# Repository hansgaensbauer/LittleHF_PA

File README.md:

# Little HF MRF101AN PA

This is a HF power amplifier using the MRF101AN RF LDMOS transistor.

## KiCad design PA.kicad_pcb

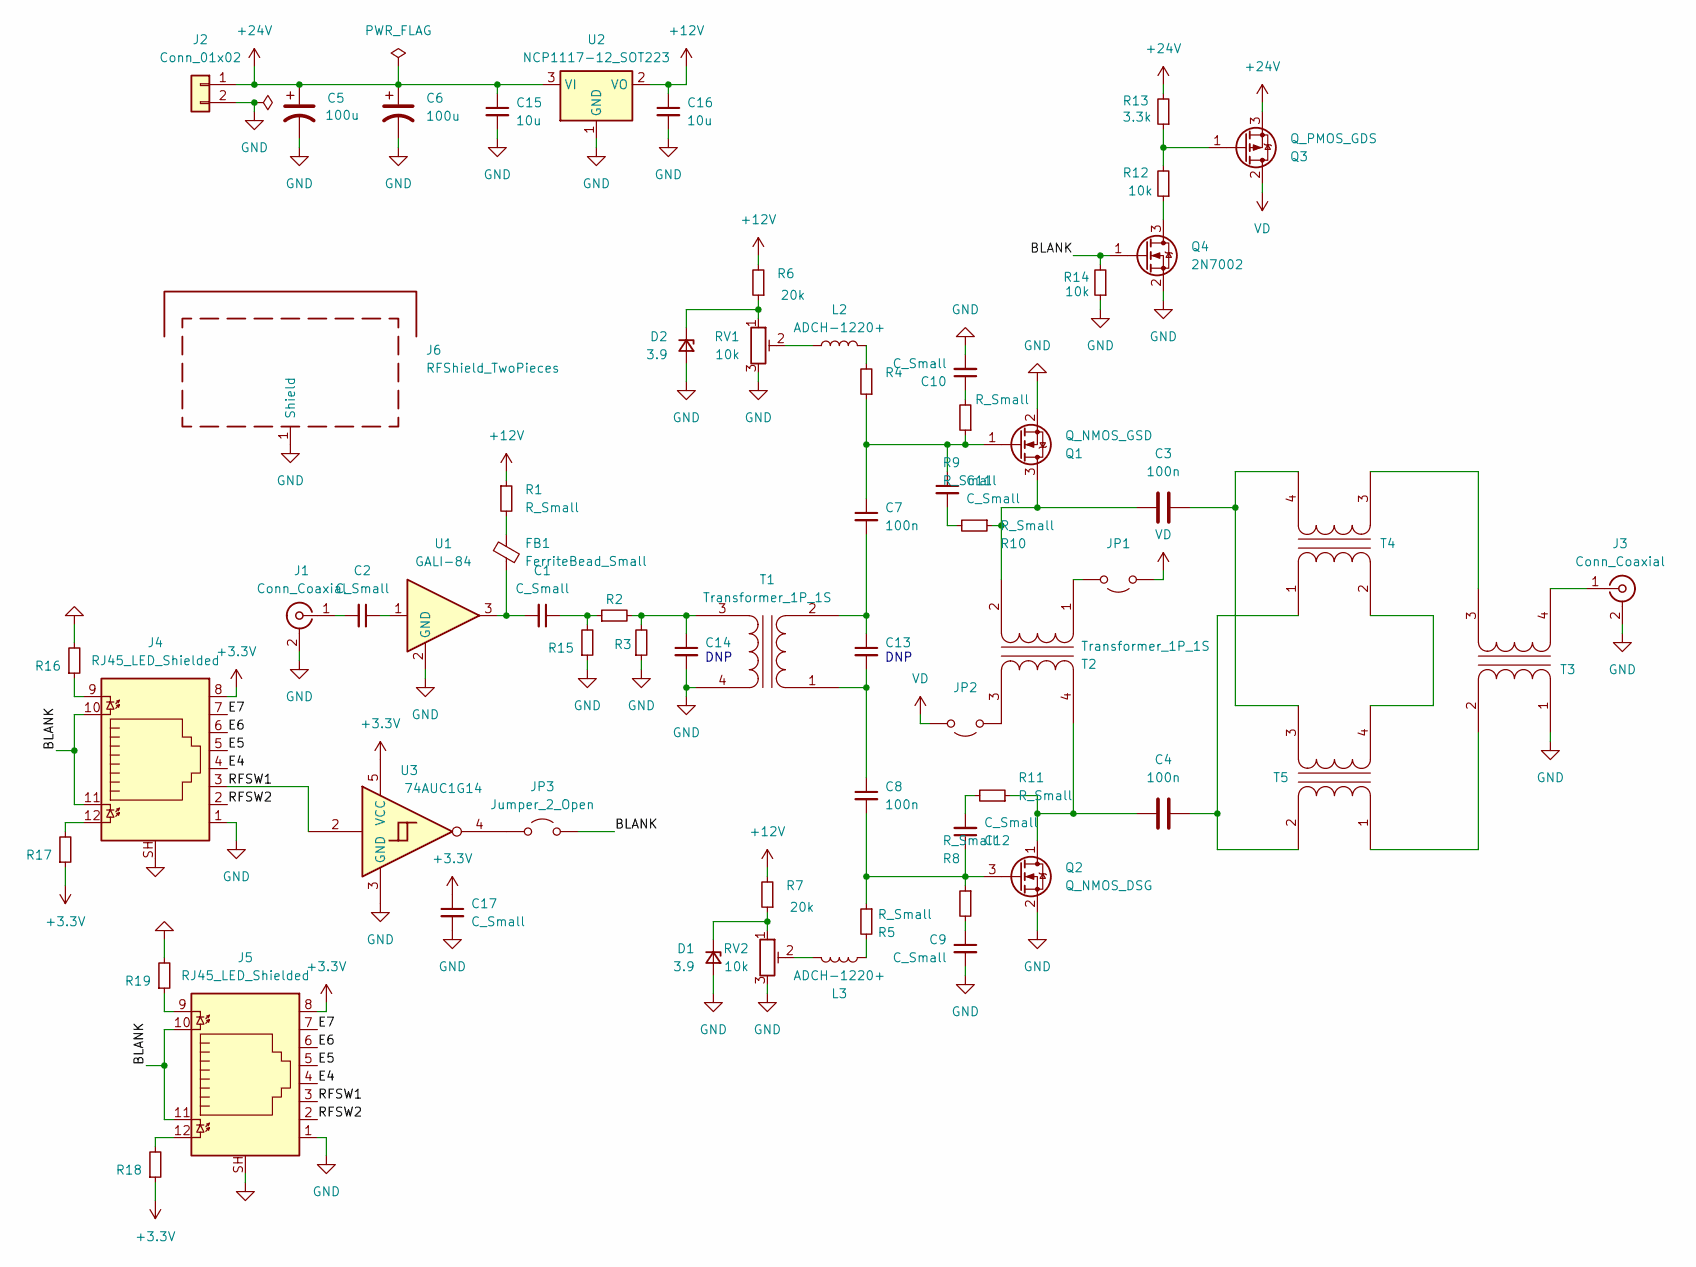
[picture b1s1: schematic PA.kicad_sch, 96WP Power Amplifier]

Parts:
C1, C2, C9, C10, C11, C12, C17: C_Small; C_0603_1608Metric
C3, C4: 100n; C_1812_4532Metric
C5, C6: 100u; CP_Elec_10x12.5
C7, C8, C13, C14: 100n; C_0603_1608Metric
C15, C16: 10u; C_1206_3216Metric
D1, D2: 3.9; D_SOD-123
FB1: FerriteBead_Small; L_1206_3216Metric
J1: Conn_Coaxial; SMA_Samtec_SMA-J-P-X-ST-EM1_EdgeMount
J2: Conn_01x02; Powerpole_1x2
J3: Conn_Coaxial; 538-73171-0780
J4, J5: RJ45_LED_Shielded; RJ45_Amphenol_RJHSE538X
J6: RFShield_TwoPieces; Wuerth_36103205_20x20mm
JP1, JP2: Jumper_2_Open; PinHeader_1x02_P2.54mm_Vertical_SMD_Pin1Left
JP3: Jumper_2_Open; R_0603_1608Metric
L2, L3: ADCH-1220+; Mini-Circuits_CD637_H5.23mm
Q1: Q_NMOS_GSD; TO-220-3_Horizontal_SMD
Q2: Q_NMOS_DSG; TO-220-3_Horizontal_SMD
Q3: Q_PMOS_GDS; TO-252-2
Q4: 2N7002; SOT-23
R1, R2, R3, R4, R5, R8, R9, R10, R11, R15, R16, R17, R18, R19: R_Small; R_0603_1608Metric
R6, R7: 20k; R_0603_1608Metric
R12, R14: 10k; R_0603_1608Metric
R13: 3.3k; R_0603_1608Metric
RV1, RV2: 10k; Potentiometer_Bourns_3269W_Vertical
T1: Transformer_1P_1S; Transformer_1P1S_13x13_Binocular
T2: Transformer_1P_1S; Transformer_Toroid_Horizontal_D18.0mm
T3, T4, T5: Transformer_1P_1S; Transformer_TLT_29x30
U1: GALI-84; SOT-89-3
U2: NCP1117-12_SOT223; SOT-223-3_TabPin2
U3: 74AUC1G14; SOT-23-5

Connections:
+3.3V: C17.1, J4.8, J5.8, R17.1, R18.1, U3.5 (VCC)
+12V: C16.1, R1.1, R6.2, R7.2, U2.2 (VO)
+24V: C5.1, C6.1, C15.1, J2.1, Q3.3 (S), R13.2, U2.3 (VI)
/BLANK: J4.10, J4.11, J5.10, J5.11, JP3.2 (B), Q4.1 (G), R14.2
/E4: J4.4, J5.4
/E5: J4.5, J5.5
/E6: J4.6, J5.6
/E7: J4.7, J5.7
/RFSW1: J4.3, J5.3, U3.2
/RFSW2: J4.2, J5.2
GND: C5.2, C6.2, C9.2, C10.2, C14.2, C15.2, C16.2, C17.2, D1.2 (A), D2.2 (A), J1.2 (Ext), J2.2, J3.2 (Ext), J4.1, J4.SH, J5.1, J5.SH, J6.1 (Shield), Q1.2 (S), Q2.2 (S), Q4.2 (S), R3.1, R14.1, R15.1, R16.2, R19.2, RV1.3, RV2.3, T1.4 (SB), T3.1 (AA), U1.2 (GND), U2.1 (GND), U3.3 (GND)
unnamed: C1.1, R2.1, R15.2
unnamed: C1.2, FB1.2, U1.3
unnamed: C2.1, U1.1
unnamed: C9.1, R8.2
unnamed: C10.1, R9.2
unnamed: C11.2, R10.2
unnamed: C12.2, R11.2
unnamed: D1.1 (K), R7.1, RV2.1
unnamed: D2.1 (K), R6.1, RV1.1
unnamed: FB1.1, R1.2
unnamed: C2.2, J1.1 (In)
unnamed: J3.1 (In), T3.4 (SB)
unnamed: J4.9, R16.1
unnamed: J4.12, R17.2
unnamed: J5.9, R19.1
unnamed: J5.12, R18.2
unnamed: JP1.2 (B), T2.1 (AA)
unnamed: JP2.2 (B), T2.3 (SA)
unnamed: JP3.1 (A), U3.4
unnamed: L2.4 (RFGND), RV1.2
unnamed: L2.1 (RFIN), R4.2
unnamed: L3.4 (RFGND), RV2.2
unnamed: L3.1 (RFIN), R5.2
unnamed: C3.1, Q1.3 (D), R10.1, T2.2 (AB)
unnamed: C7.1, C11.1, Q1.1 (G), R4.1, R9.1
unnamed: C4.1, Q2.1 (D), R11.1, T2.4 (SB)
unnamed: C8.2, C12.1, Q2.3 (G), R5.1, R8.1
unnamed: Q3.1 (G), R12.2, R13.1
unnamed: Q4.3 (D), R12.1
unnamed: C8.1, C13.2, T1.1 (AA)
unnamed: C7.2, C13.1, T1.2 (AB)
unnamed: C14.1, R2.2, R3.2, T1.3 (SA)
unnamed: T3.2 (AB), T5.1 (AA)
unnamed: T3.3 (SA), T4.3 (SA)
unnamed: C4.2, T4.1 (AA), T5.2 (AB)
unnamed: T4.2 (AB), T5.4 (SB)
unnamed: C3.2, T4.4 (SB), T5.3 (SA)
VD: JP1.1 (A), JP2.1 (A), Q3.2 (D)

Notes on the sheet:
DNP

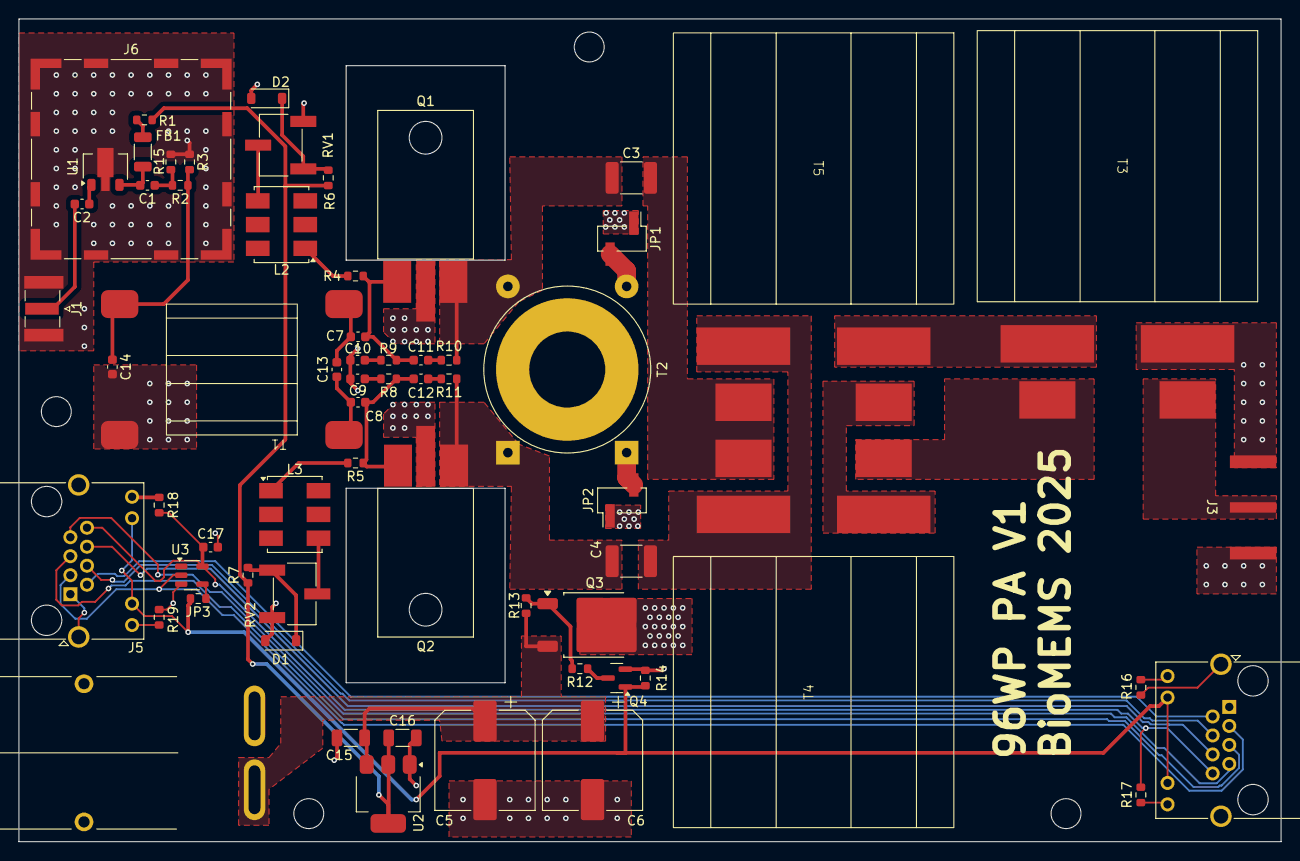
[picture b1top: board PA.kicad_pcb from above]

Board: 2 copper layers, 135.0 x 88.0 mm, 64 parts (0 on the bottom side), 49 nets.
